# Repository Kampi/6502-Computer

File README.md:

# 6502 Computer

## Table of Contents

- [6502 Computer](#6502-computer)
  - [Table of Contents](#table-of-contents)
  - [About](#about)
  - [Examples](#examples)
  - [History](#history)
  - [Maintainer](#maintainer)

## About

A simple W65C02 based computer. This project should realize an old-style computer with peripheral interfaces like PS/2, LCD, VGA, etc.

Please check the [wiki](https://gitlab.com/Kampi/6502-computer/-/wikis/home) or write an e-mail to [DanielKampert@kampis-elektroecke.de](DanielKampert@kampis-elektroecke.de) if you have any questions.

> You can use [this](https://www.mouser.de/ProductDetail/Aries-Electronics/28-6554-11?qs=%2Fha2pyFaduhJzW47Xe0mc6AQy9aNg75kRj%2FLuQHFHUG0ReEYpRrMQA%3D%3D) ZIF socket for the EEPROM instead of the normal DIP socket for an easier mounting of the EEPROM.

## Tutorial

The `tutorial` folder of the repository contains the software examples from my [website](https://www.kampis-elektroecke.de/6502-computer/).

| **Tutorial** | **Description** |
|---|---|
| Lession 1 | Small program to check out how the compiler works and to test the communication between microprocessor, RAM and EEPROM. |
| Lession 2 | Simple program to learn the stack mechanics. |

## History

| **Version**  | **Description**                            	| **Date**   |
|:------------:|:----------------------------------------------:|:----------:|
| 0.1          | First hardware release.                     	| 18.10.2019 |
| 0.2          | Fix different hardware bugs, add new features. | 10.05.2021 |
| 0.3          |  |  |

## Maintainer

- [Daniel Kampert](mailto:DanielKampert@kampis-elektroecke.de)

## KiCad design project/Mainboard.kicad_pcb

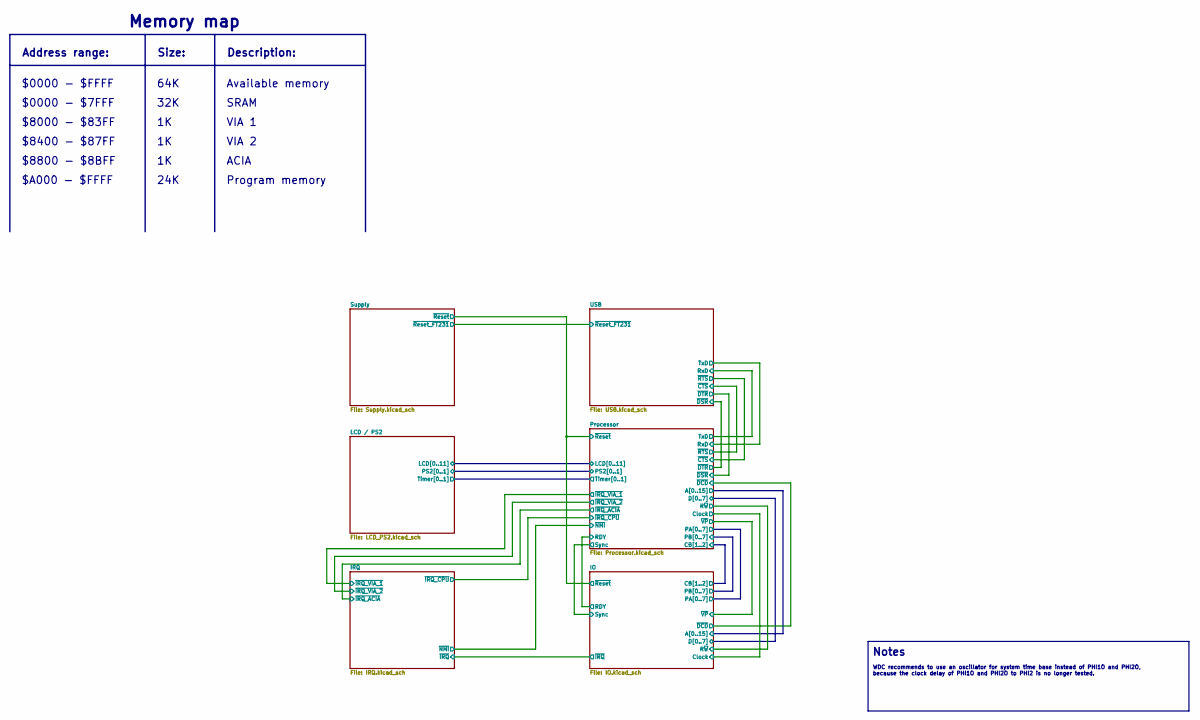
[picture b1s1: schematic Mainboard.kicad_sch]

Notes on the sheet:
$8000 - $83FF
Notes
$8400 - $87FF
64K
32K
ACIA
WDC recommends to use an oscillator for system time base instead of PHI1O and PHI2O, because the clock delay of PHI1O and PHI2O to PHI2 is no longer tested.
Size:
$8800 - $8BFF
Memory map
Program memory
Available memory
$0000 - $7FFF
SRAM
Address range:
24K
Description:
$0000 - $FFFF
$A000 - $FFFF
VIA 2
VIA 1

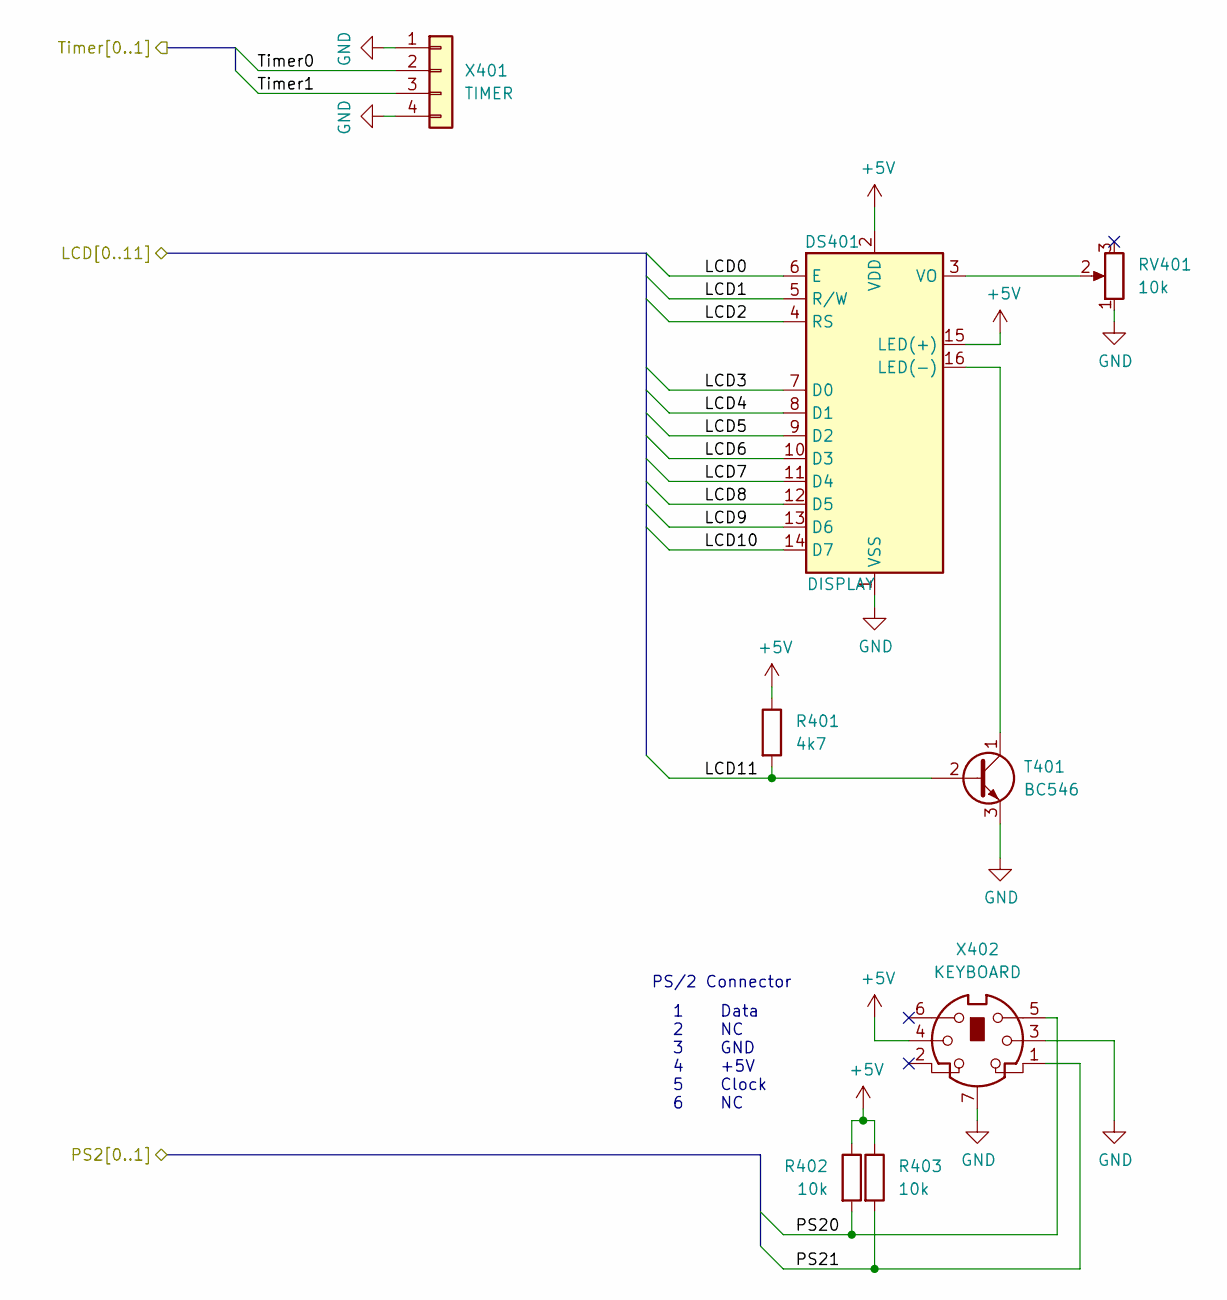
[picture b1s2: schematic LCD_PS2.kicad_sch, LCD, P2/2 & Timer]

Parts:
DS401: DISPLAY; WC1602A
R401: 4k7; R_Axial_DIN0207_L6.3mm_D2.5mm_P7.62mm_Horizontal
R402, R403: 10k; R_Axial_DIN0207_L6.3mm_D2.5mm_P7.62mm_Horizontal
RV401: 10k; Bourns_3386P_Vertical
T401: BC546; TO-92_Inline
X401: TIMER; PinHeader_1x04_P2.54mm_Vertical
X402: KEYBOARD; Mini-DIN_TE_Female_6Pin_2rows

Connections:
+5V: DS401.2 (VDD), DS401.15 (LED(+)), R401.1, R402.1, R403.1, X402.4; also elsewhere on the board
/LCD / PS2/LCD0: DS401.6 (E); also elsewhere on the board
/LCD / PS2/LCD1: DS401.5 (R/W); also elsewhere on the board
/LCD / PS2/LCD2: DS401.4 (RS); also elsewhere on the board
/LCD / PS2/LCD3: DS401.7 (D0); also elsewhere on the board
/LCD / PS2/LCD4: DS401.8 (D1); also elsewhere on the board
/LCD / PS2/LCD5: DS401.9 (D2); also elsewhere on the board
/LCD / PS2/LCD6: DS401.10 (D3); also elsewhere on the board
/LCD / PS2/LCD7: DS401.11 (D4); also elsewhere on the board
/LCD / PS2/LCD8: DS401.12 (D5); also elsewhere on the board
/LCD / PS2/LCD9: DS401.13 (D6); also elsewhere on the board
/LCD / PS2/LCD10: DS401.14 (D7); also elsewhere on the board
/LCD / PS2/LCD11: R401.2, T401.2 (B); also elsewhere on the board
/LCD / PS2/PS20: R402.2, X402.5; also elsewhere on the board
/LCD / PS2/PS21: R403.2, X402.1; also elsewhere on the board
/LCD / PS2/Timer0: X401.2; also elsewhere on the board
/LCD / PS2/Timer1: X401.3; also elsewhere on the board
GND: DS401.1 (VSS), RV401.1, T401.3 (E), X401.1, X401.4, X402.3, X402.7; also elsewhere on the board
unnamed: DS401.16 (LED(-)), T401.1 (C)
unnamed: DS401.3 (VO), RV401.2

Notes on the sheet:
PS/2 Connector
Data NC GND +5V Clock NC
1 2 3 4 5 6

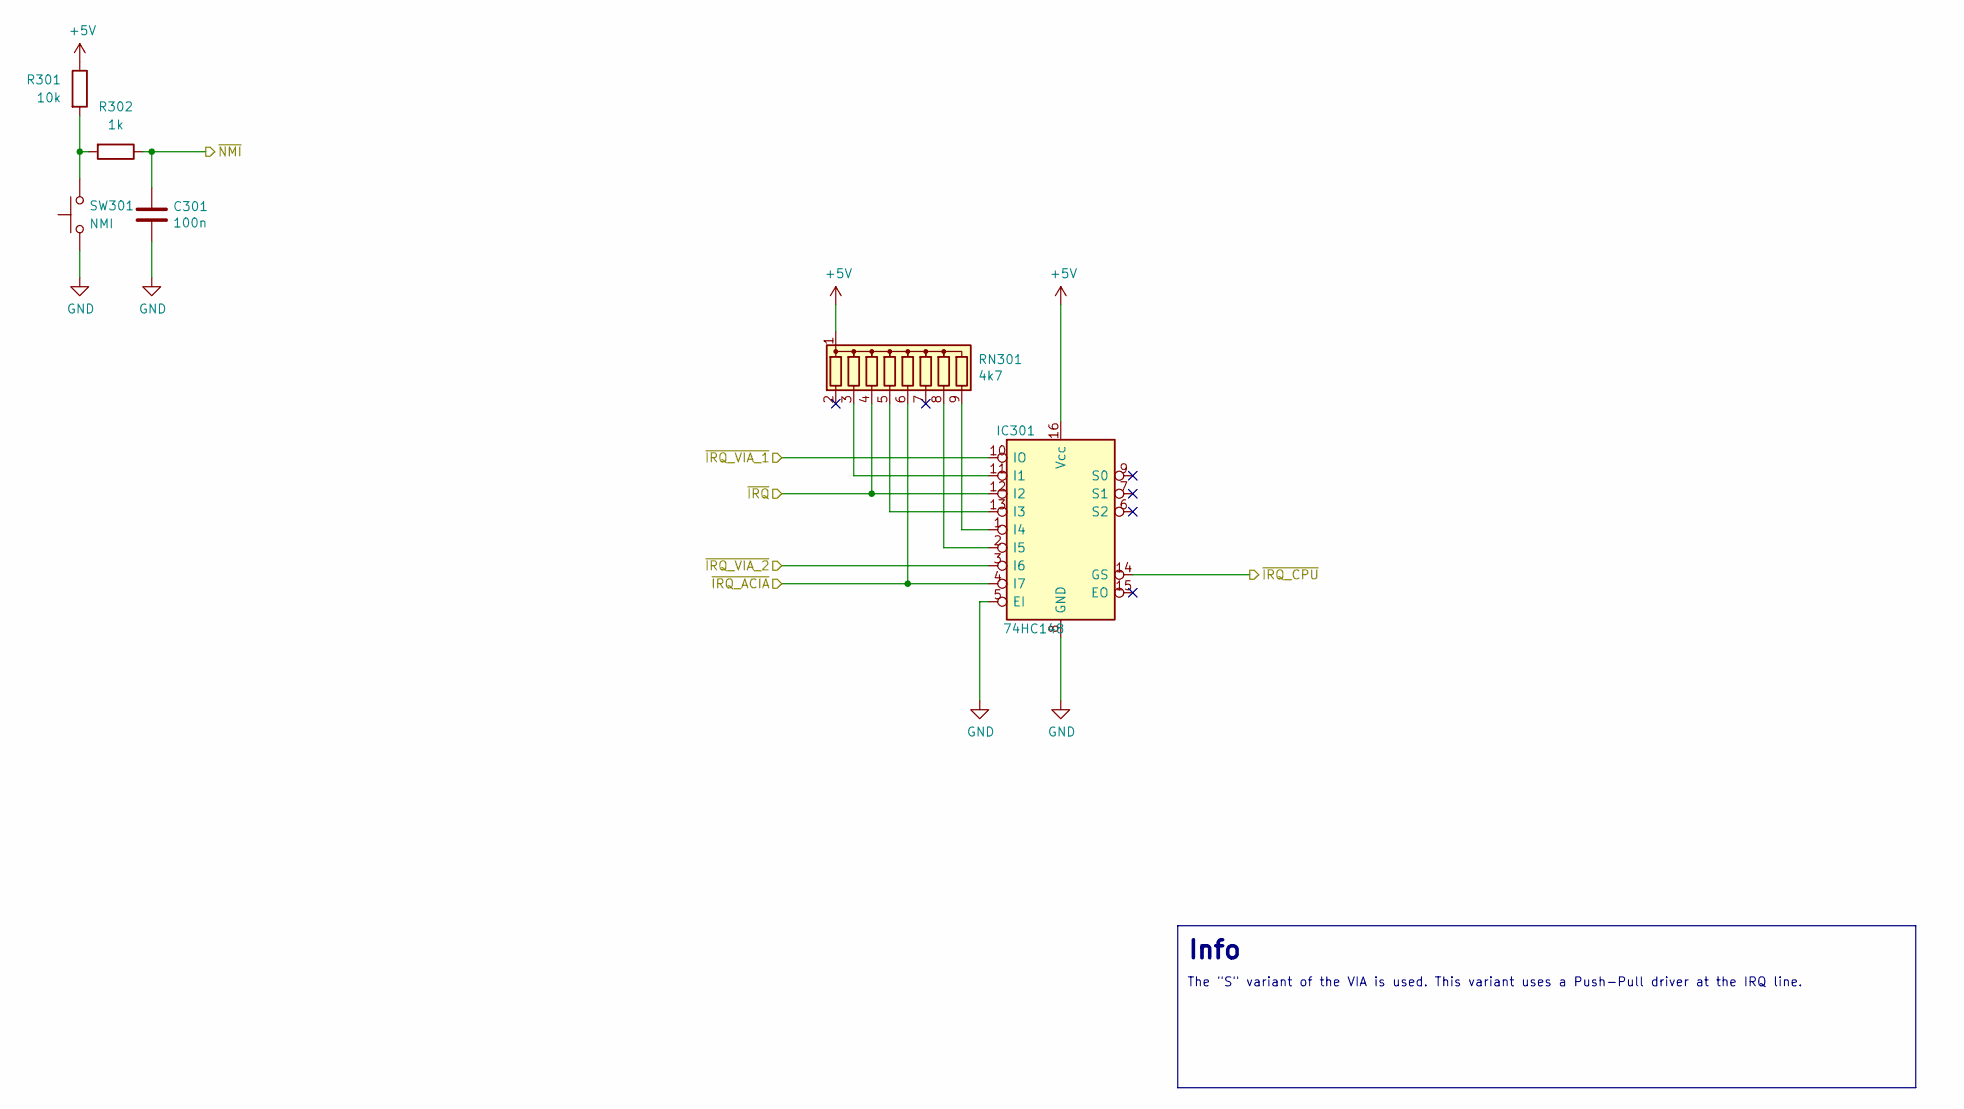
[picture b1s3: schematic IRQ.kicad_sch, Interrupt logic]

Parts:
C301: 100n; C_Rect_L4.0mm_W2.5mm_P2.50mm
IC301: 74HC148; DIP-16_W7.62mm_LongPads
R301: 10k; R_Axial_DIN0207_L6.3mm_D2.5mm_P7.62mm_Horizontal
R302: 1k; R_Axial_DIN0207_L6.3mm_D2.5mm_P7.62mm_Horizontal
RN301: 4k7; R_Array_SIP9
SW301: NMI; SW_PUSH_6mm_H4.3mm

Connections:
+5V: IC301.16 (Vcc), R301.1, RN301.1 (common); also elsewhere on the board
/IO/~IRQ: IC301.12 (I2), RN301.4 (R3); also elsewhere on the board
/IRQ/~IRQ_ACIA: IC301.4 (I7), RN301.6 (R5); also elsewhere on the board
/IRQ/~IRQ_CPU: IC301.14 (GS); also elsewhere on the board
/IRQ/~IRQ_VIA_1: IC301.10 (IO); also elsewhere on the board
/IRQ/~IRQ_VIA_2: IC301.3 (I6); also elsewhere on the board
/IRQ/~NMI: C301.1, R302.1; also elsewhere on the board
GND: C301.2, IC301.5 (EI), IC301.8 (GND), SW301.1; also elsewhere on the board
unnamed: IC301.11 (I1), RN301.3 (R2)
unnamed: IC301.13 (I3), RN301.5 (R4)
unnamed: IC301.1 (I4), RN301.9 (R8)
unnamed: IC301.2 (I5), RN301.8 (R7)
unnamed: R301.2, R302.2, SW301.2

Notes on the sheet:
Info
The "S" variant of the VIA is used. This variant uses a Push-Pull driver at the IRQ line.

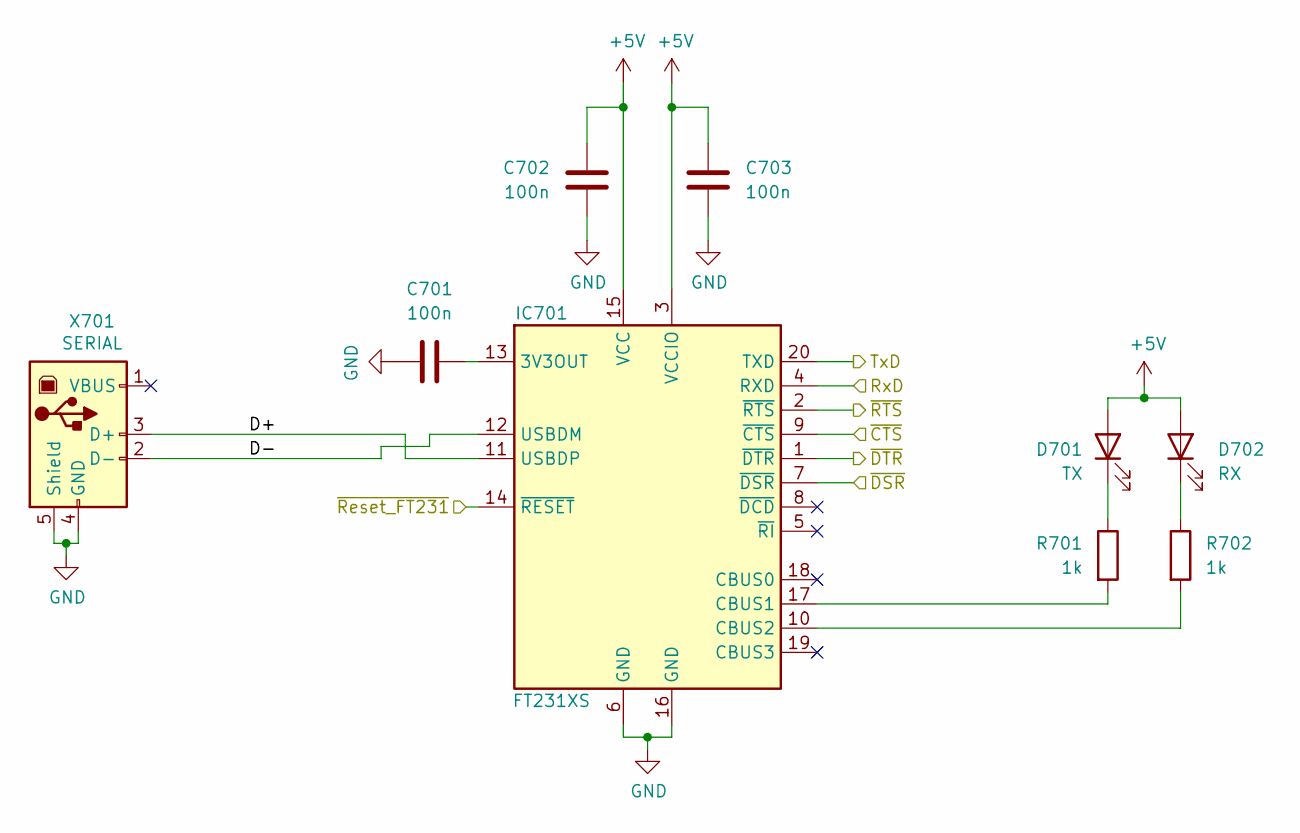
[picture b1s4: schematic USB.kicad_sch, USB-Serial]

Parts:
C701, C702, C703: 100n; C_0805_2012Metric
D701: TX; LED_0805_2012Metric
D702: RX; LED_0805_2012Metric
IC701: FT231XS; SSOP-20_3.9x8.7mm_P0.635mm
R701, R702: 1k; R_0805_2012Metric
X701: SERIAL; USB-B_TE_2923042_Horizontal

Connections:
+5V: C702.1, C703.1, D701.2 (A), D702.2 (A), IC701.3 (VCCIO), IC701.15 (VCC); also elsewhere on the board
/Processor/RxD: IC701.20 (TXD); also elsewhere on the board
/Processor/TxD: IC701.4 (RXD); also elsewhere on the board
/Processor/~CTS: IC701.2 (~RTS); also elsewhere on the board
/Processor/~DSR: IC701.1 (~DTR); also elsewhere on the board
/Processor/~DTR: IC701.7 (~DSR); also elsewhere on the board
/Processor/~RTS: IC701.9 (~CTS); also elsewhere on the board
/Supply/~Reset_FT231: IC701.14 (~RESET); also elsewhere on the board
/USB/D+: IC701.11 (USBDP), X701.3 (D+)
/USB/D-: IC701.12 (USBDM), X701.2 (D-)
GND: C701.1, C702.2, C703.2, IC701.6 (GND), IC701.16 (GND), X701.4 (GND), X701.5 (Shield); also elsewhere on the board
unnamed: D701.1 (K), R701.1
unnamed: D702.1 (K), R702.1
unnamed: C701.2, IC701.13 (3V3OUT)
unnamed: IC701.17 (CBUS1), R701.2
unnamed: IC701.10 (CBUS2), R702.2

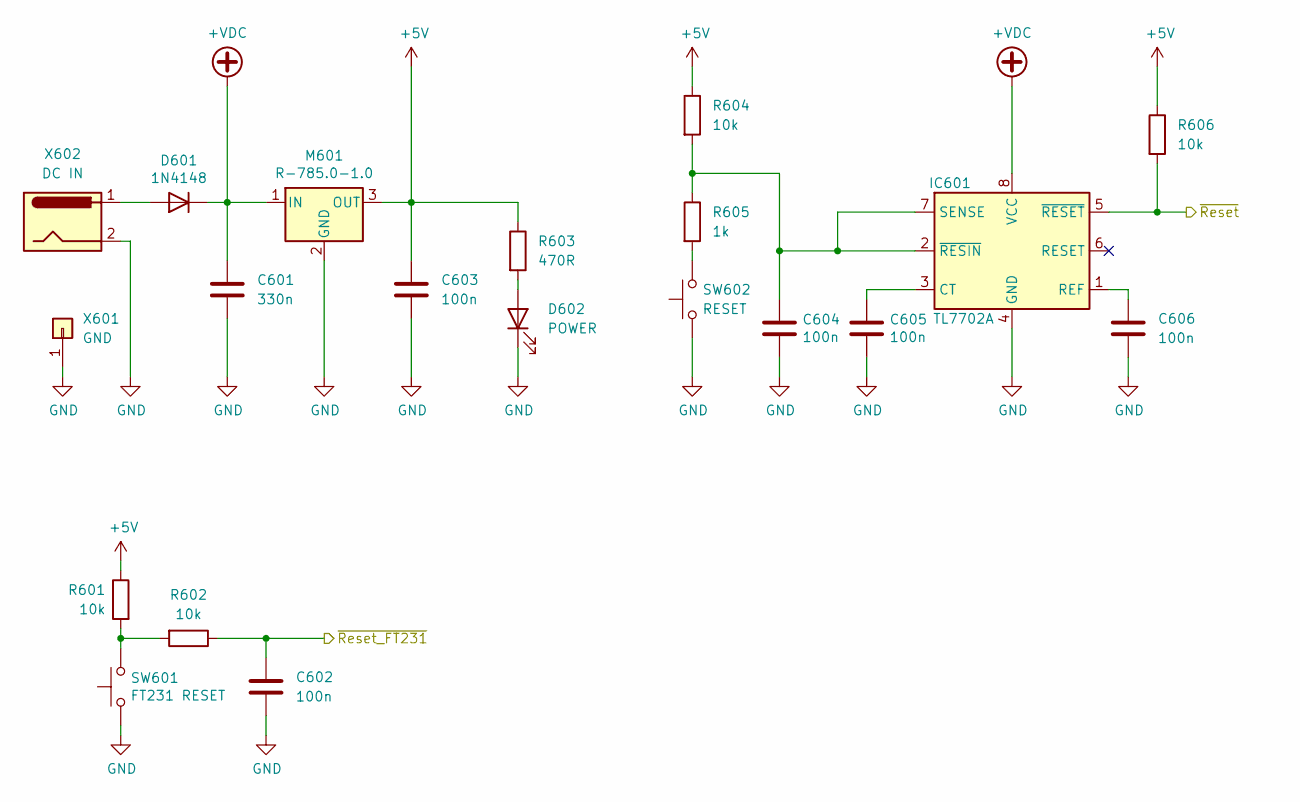
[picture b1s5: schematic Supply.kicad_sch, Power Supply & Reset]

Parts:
C601: 330n; C_Rect_L4.0mm_W2.5mm_P2.50mm
C602, C603, C604, C605, C606: 100n; C_Rect_L4.0mm_W2.5mm_P2.50mm
D601: 1N4148; D_SOD-123
D602: POWER; LED_D5.0mm
IC601: TL7702A; DIP-8_W7.62mm_LongPads
M601: R-785.0-1.0; Converter_DCDC_RECOM_R-78E-0.5_THT
R601, R602, R604, R606: 10k; R_Axial_DIN0207_L6.3mm_D2.5mm_P7.62mm_Horizontal
R603: 470R; R_Axial_DIN0207_L6.3mm_D2.5mm_P7.62mm_Horizontal
R605: 1k; R_Axial_DIN0207_L6.3mm_D2.5mm_P7.62mm_Horizontal
SW601: FT231 RESET; SW_PUSH_6mm_H4.3mm
SW602: RESET; SW_PUSH_6mm_H4.3mm
X601: GND; PinHeader_1x01_P2.54mm_Vertical
X602: DC IN; BarrelJack_Wuerth_6941xx301002

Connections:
+5V: C603.1, M601.3 (OUT), R601.1, R603.1, R604.1, R606.1; also elsewhere on the board
+VDC: C601.1, D601.1 (K), IC601.8 (VCC), M601.1 (IN)
/IO/~Reset: IC601.5 (~RESET), R606.2; also elsewhere on the board
/Supply/~Reset_FT231: C602.1, R602.1; also elsewhere on the board
GND: C601.2, C602.2, C603.2, C604.2, C605.2, C606.2, D602.1 (K), IC601.4 (GND), M601.2 (GND), SW601.1, SW602.1, X601.1, X602.2; also elsewhere on the board
unnamed: D601.2 (A), X602.1
unnamed: D602.2 (A), R603.2
unnamed: C605.1, IC601.3 (CT)
unnamed: C606.1, IC601.1 (REF)
unnamed: C604.1, IC601.2 (~RESIN), IC601.7 (SENSE), R604.2, R605.1
unnamed: R601.2, R602.2, SW601.2
unnamed: R605.2, SW602.2

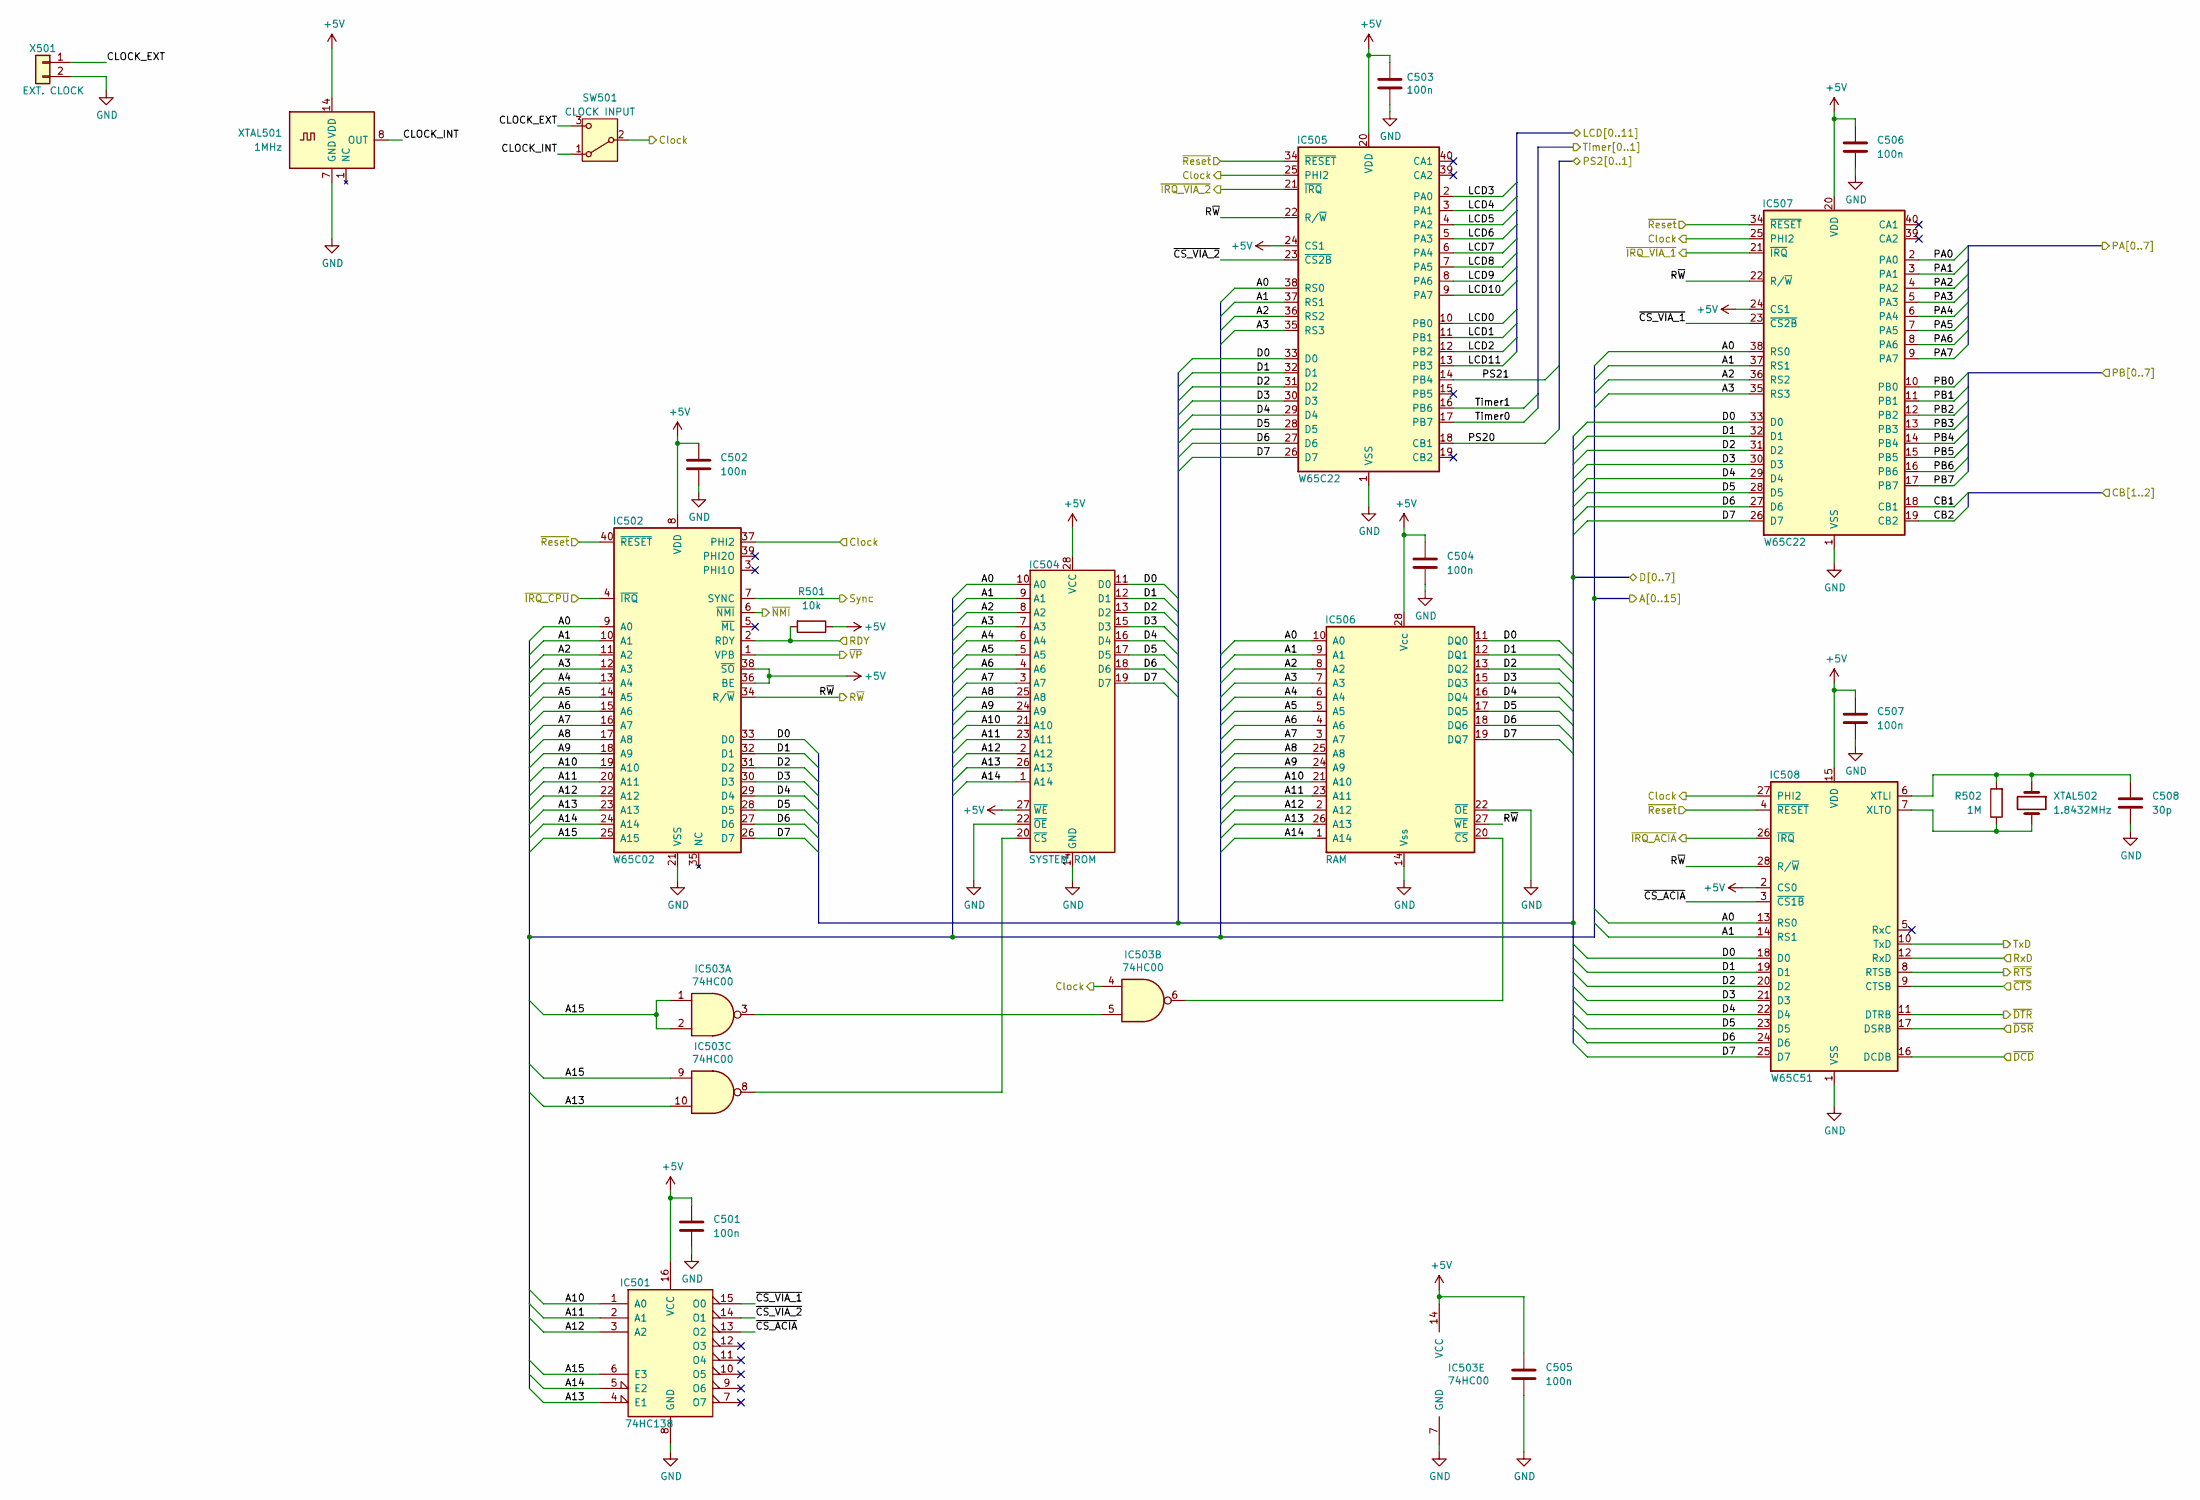
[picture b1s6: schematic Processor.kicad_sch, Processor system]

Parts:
C501, C502, C503, C504, C505, C506, C507: 100n; C_Rect_L4.0mm_W2.5mm_P2.50mm
C508: 30p; C_Rect_L4.0mm_W2.5mm_P2.50mm
IC501: 74HC138; DIP-16_W7.62mm_LongPads
IC502: W65C02; DIP-40_W15.24mm_LongPads
IC503: 74HC00; DIP-14_W7.62mm_LongPads
IC504: SYSTEM ROM; DIP-28_W15.24mm_LongPads
IC505, IC507: W65C22; DIP-40_W15.24mm_LongPads
IC506: RAM; DIP-28_W15.24mm_LongPads
IC508: W65C51; DIP-28_W15.24mm_LongPads
R501: 10k; R_Axial_DIN0207_L6.3mm_D2.5mm_P7.62mm_Horizontal
R502: 1M; R_Axial_DIN0207_L6.3mm_D2.5mm_P7.62mm_Horizontal
SW501: CLOCK INPUT; SW_E-Switch_EG1271_DPDT
X501: EXT. CLOCK; SMA_Amphenol_901-144_Vertical
XTAL501: 1MHz; Oscillator_DIP-14
XTAL502: 1.8432MHz; Crystal_HC49-U_Vertical

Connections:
+5V: C501.1, C502.1, C503.1, C504.1, C505.1, C506.1, C507.1, IC501.16 (VCC), IC502.8 (VDD), IC502.36 (BE), IC502.38 (~SO), IC503.14 (VCC), IC504.27 (~WE), IC504.28 (VCC), IC505.20 (VDD), IC505.24 (CS1), IC506.28 (Vcc), IC507.20 (VDD), IC507.24 (CS1), IC508.2 (CS0), IC508.15 (VDD), R501.1, XTAL501.14 (VDD); also elsewhere on the board
/IO/A0: IC502.9 (A0), IC504.10 (A0), IC505.38 (RS0), IC506.10 (A0), IC507.38 (RS0), IC508.13 (RS0); also elsewhere on the board
/IO/A1: IC502.10 (A1), IC504.9 (A1), IC505.37 (RS1), IC506.9 (A1), IC507.37 (RS1), IC508.14 (RS1); also elsewhere on the board
/IO/A2: IC502.11 (A2), IC504.8 (A2), IC505.36 (RS2), IC506.8 (A2), IC507.36 (RS2); also elsewhere on the board
/IO/A3: IC502.12 (A3), IC504.7 (A3), IC505.35 (RS3), IC506.7 (A3), IC507.35 (RS3); also elsewhere on the board
/IO/A4: IC502.13 (A4), IC504.6 (A4), IC506.6 (A4); also elsewhere on the board
/IO/A5: IC502.14 (A5), IC504.5 (A5), IC506.5 (A5); also elsewhere on the board
/IO/A6: IC502.15 (A6), IC504.4 (A6), IC506.4 (A6); also elsewhere on the board
/IO/A7: IC502.16 (A7), IC504.3 (A7), IC506.3 (A7); also elsewhere on the board
/IO/A8: IC502.17 (A8), IC504.25 (A8), IC506.25 (A8); also elsewhere on the board
/IO/A9: IC502.18 (A9), IC504.24 (A9), IC506.24 (A9); also elsewhere on the board
/IO/A10: IC501.1 (A0), IC502.19 (A10), IC504.21 (A10), IC506.21 (A10); also elsewhere on the board
/IO/A11: IC501.2 (A1), IC502.20 (A11), IC504.23 (A11), IC506.23 (A11); also elsewhere on the board
/IO/A12: IC501.3 (A2), IC502.22 (A12), IC504.2 (A12), IC506.2 (A12); also elsewhere on the board
/IO/A13: IC501.4 (E1), IC502.23 (A13), IC503.10, IC504.26 (A13), IC506.26 (A13); also elsewhere on the board
/IO/A14: IC501.5 (E2), IC502.24 (A14), IC504.1 (A14), IC506.1 (A14); also elsewhere on the board
/IO/A15: IC501.6 (E3), IC502.25 (A15), IC503.1, IC503.2, IC503.9; also elsewhere on the board
/IO/CB1: IC507.18 (CB1); also elsewhere on the board
/IO/CB2: IC507.19 (CB2); also elsewhere on the board
/IO/Clock: IC502.37 (PHI2), IC503.4, IC505.25 (PHI2), IC507.25 (PHI2), IC508.27 (PHI2), SW501.2 (B); also elsewhere on the board
/IO/D0: IC502.33 (D0), IC504.11 (D0), IC505.33 (D0), IC506.11 (DQ0), IC507.33 (D0), IC508.18 (D0); also elsewhere on the board
/IO/D1: IC502.32 (D1), IC504.12 (D1), IC505.32 (D1), IC506.12 (DQ1), IC507.32 (D1), IC508.19 (D1); also elsewhere on the board
/IO/D2: IC502.31 (D2), IC504.13 (D2), IC505.31 (D2), IC506.13 (DQ2), IC507.31 (D2), IC508.20 (D2); also elsewhere on the board
/IO/D3: IC502.30 (D3), IC504.15 (D3), IC505.30 (D3), IC506.15 (DQ3), IC507.30 (D3), IC508.21 (D3); also elsewhere on the board
/IO/D4: IC502.29 (D4), IC504.16 (D4), IC505.29 (D4), IC506.16 (DQ4), IC507.29 (D4), IC508.22 (D4); also elsewhere on the board
/IO/D5: IC502.28 (D5), IC504.17 (D5), IC505.28 (D5), IC506.17 (DQ5), IC507.28 (D5), IC508.23 (D5); also elsewhere on the board
/IO/D6: IC502.27 (D6), IC504.18 (D6), IC505.27 (D6), IC506.18 (DQ6), IC507.27 (D6), IC508.24 (D6); also elsewhere on the board
/IO/D7: IC502.26 (D7), IC504.19 (D7), IC505.26 (D7), IC506.19 (DQ7), IC507.26 (D7), IC508.25 (D7); also elsewhere on the board
/IO/PA0: IC507.2 (PA0); also elsewhere on the board
/IO/PA1: IC507.3 (PA1); also elsewhere on the board
/IO/PA2: IC507.4 (PA2); also elsewhere on the board
/IO/PA3: IC507.5 (PA3); also elsewhere on the board
/IO/PA4: IC507.6 (PA4); also elsewhere on the board
/IO/PA5: IC507.7 (PA5); also elsewhere on the board
/IO/PA6: IC507.8 (PA6); also elsewhere on the board
/IO/PA7: IC507.9 (PA7); also elsewhere on the board
/IO/PB0: IC507.10 (PB0); also elsewhere on the board
/IO/PB1: IC507.11 (PB1); also elsewhere on the board
/IO/PB2: IC507.12 (PB2); also elsewhere on the board
/IO/PB3: IC507.13 (PB3); also elsewhere on the board
/IO/PB4: IC507.14 (PB4); also elsewhere on the board
/IO/PB5: IC507.15 (PB5); also elsewhere on the board
/IO/PB6: IC507.16 (PB6); also elsewhere on the board
/IO/PB7: IC507.17 (PB7); also elsewhere on the board
/IO/RDY: IC502.2 (RDY), R501.2; also elsewhere on the board
/IO/Sync: IC502.7 (SYNC); also elsewhere on the board
/IO/~DCD: IC508.16 (DCDB); also elsewhere on the board
/IO/~Reset: IC502.40 (~RESET), IC505.34 (~RESET), IC507.34 (~RESET), IC508.4 (~RESET); also elsewhere on the board
/IO/~VP: IC502.1 (VPB); also elsewhere on the board
/IRQ/~IRQ_ACIA: IC508.26 (~IRQ); also elsewhere on the board
/IRQ/~IRQ_CPU: IC502.4 (~IRQ); also elsewhere on the board
/IRQ/~IRQ_VIA_1: IC507.21 (~IRQ); also elsewhere on the board
/IRQ/~IRQ_VIA_2: IC505.21 (~IRQ); also elsewhere on the board
/IRQ/~NMI: IC502.6 (~NMI); also elsewhere on the board
/LCD / PS2/LCD0: IC505.10 (PB0); also elsewhere on the board
/LCD / PS2/LCD1: IC505.11 (PB1); also elsewhere on the board
/LCD / PS2/LCD2: IC505.12 (PB2); also elsewhere on the board
/LCD / PS2/LCD3: IC505.2 (PA0); also elsewhere on the board
/LCD / PS2/LCD4: IC505.3 (PA1); also elsewhere on the board
/LCD / PS2/LCD5: IC505.4 (PA2); also elsewhere on the board
/LCD / PS2/LCD6: IC505.5 (PA3); also elsewhere on the board
/LCD / PS2/LCD7: IC505.6 (PA4); also elsewhere on the board
/LCD / PS2/LCD8: IC505.7 (PA5); also elsewhere on the board
/LCD / PS2/LCD9: IC505.8 (PA6); also elsewhere on the board
/LCD / PS2/LCD10: IC505.9 (PA7); also elsewhere on the board
/LCD / PS2/LCD11: IC505.13 (PB3); also elsewhere on the board
/LCD / PS2/PS20: IC505.18 (CB1); also elsewhere on the board
/LCD / PS2/PS21: IC505.14 (PB4); also elsewhere on the board
/LCD / PS2/Timer0: IC505.17 (PB7); also elsewhere on the board
/LCD / PS2/Timer1: IC505.16 (PB6); also elsewhere on the board
/Processor/CLOCK_EXT: SW501.3 (C), X501.1
/Processor/CLOCK_INT: SW501.1 (A), XTAL501.8 (OUT)
/Processor/RxD: IC508.12 (RxD); also elsewhere on the board
/Processor/R~W: IC502.34 (R/~W), IC505.22 (R/~W), IC506.27 (~WE), IC507.22 (R/~W), IC508.28 (R/~W); also elsewhere on the board
/Processor/TxD: IC508.10 (TxD); also elsewhere on the board
/Processor/~CS_ACIA: IC501.13 (O2), IC508.3 (~CS1B)
/Processor/~CS_VIA_1: IC501.15 (O0), IC507.23 (~CS2B)
/Processor/~CS_VIA_2: IC501.14 (O1), IC505.23 (~CS2B)
/Processor/~CTS: IC508.9 (CTSB); also elsewhere on the board
/Processor/~DSR: IC508.17 (DSRB); also elsewhere on the board
/Processor/~DTR: IC508.11 (DTRB); also elsewhere on the board
/Processor/~RTS: IC508.8 (RTSB); also elsewhere on the board
GND: C501.2, C502.2, C503.2, C504.2, C505.2, C506.2, C507.2, C508.2, IC501.8 (GND), IC502.21 (VSS), IC503.7 (GND), IC504.14 (GND), IC504.22 (~OE), IC505.1 (VSS), IC506.14 (Vss), IC506.22 (~OE), IC507.1 (VSS), IC508.1 (VSS), X501.2, XTAL501.7 (GND); also elsewhere on the board
unnamed: IC503.3, IC503.5
unnamed: IC503.8, IC504.20 (~CS)
unnamed: IC503.6, IC506.20 (~CS)
unnamed: IC508.7 (XLTO), R502.1, XTAL502.2
unnamed: C508.1, IC508.6 (XTLI), R502.2, XTAL502.1

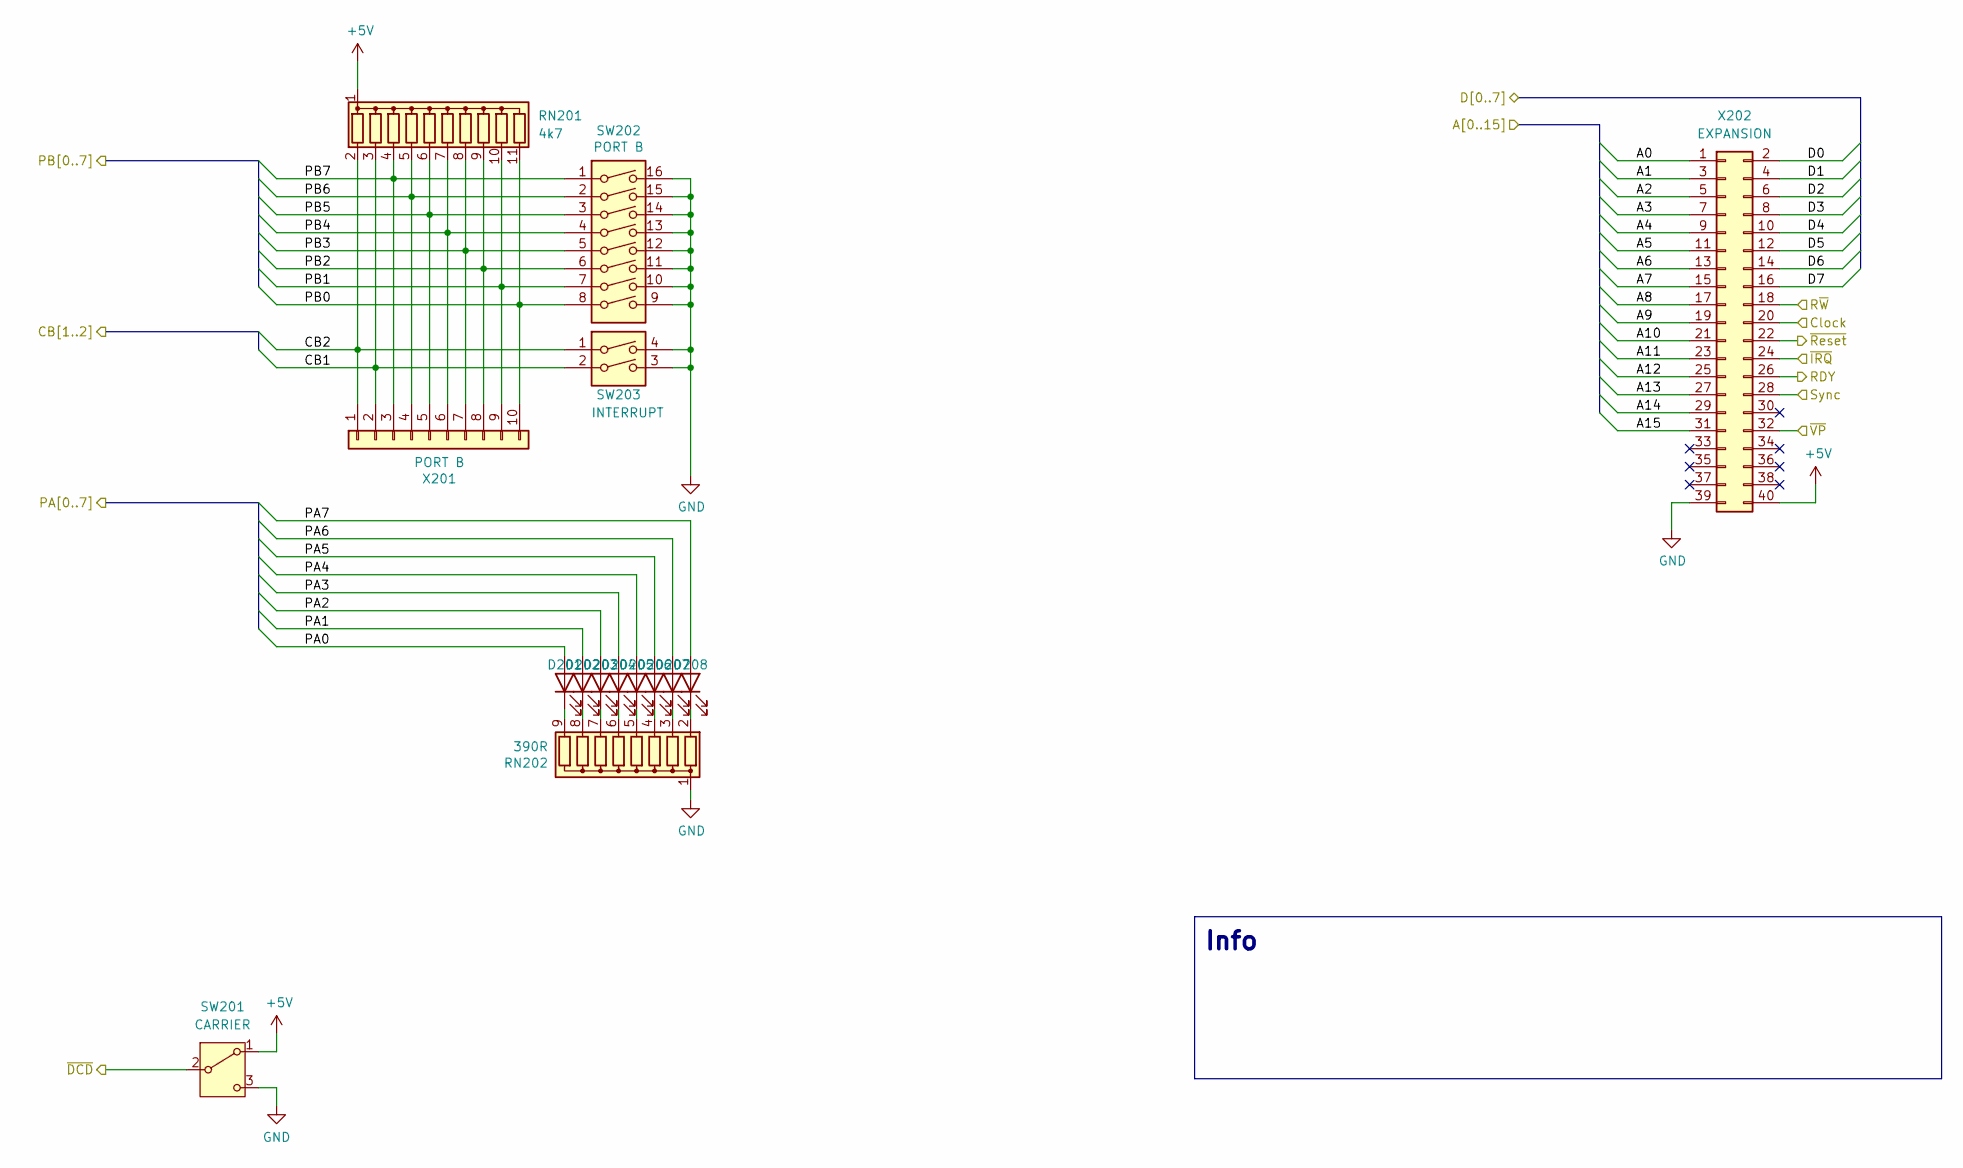
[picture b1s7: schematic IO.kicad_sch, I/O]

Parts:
D201: LED0; LED_D5.0mm
D202: LED1; LED_D5.0mm
D203: LED2; LED_D5.0mm
D204: LED3; LED_D5.0mm
D205: LED4; LED_D5.0mm
D206: LED5; LED_D5.0mm
D207: LED6; LED_D5.0mm
D208: LED7; LED_D5.0mm
RN201: 4k7; R_Array_SIP11
RN202: 390R; R_Array_SIP9
SW201: CARRIER; SW_E-Switch_EG1224_SPDT_Angled
SW202: PORT B; SW_DIP_SPSTx08_Slide_9.78x22.5mm_W7.62mm_P2.54mm
SW203: INTERRUPT; SW_DIP_SPSTx02_Slide_9.78x7.26mm_W7.62mm_P2.54mm
X201: PORT B; PinHeader_1x10_P2.54mm_Vertical
X202: EXPANSION; PinHeader_2x20_P2.54mm_Horizontal

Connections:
+5V: RN201.1 (common), SW201.1 (A), X202.40; also elsewhere on the board
/IO/A0: X202.1; also elsewhere on the board
/IO/A1: X202.3; also elsewhere on the board
/IO/A2: X202.5; also elsewhere on the board
/IO/A3: X202.7; also elsewhere on the board
/IO/A4: X202.9; also elsewhere on the board
/IO/A5: X202.11; also elsewhere on the board
/IO/A6: X202.13; also elsewhere on the board
/IO/A7: X202.15; also elsewhere on the board
/IO/A8: X202.17; also elsewhere on the board
/IO/A9: X202.19; also elsewhere on the board
/IO/A10: X202.21; also elsewhere on the board
/IO/A11: X202.23; also elsewhere on the board
/IO/A12: X202.25; also elsewhere on the board
/IO/A13: X202.27; also elsewhere on the board
/IO/A14: X202.29; also elsewhere on the board
/IO/A15: X202.31; also elsewhere on the board
/IO/CB1: RN201.3 (R2), SW203.2, X201.2; also elsewhere on the board
/IO/CB2: RN201.2 (R1), SW203.1, X201.1; also elsewhere on the board
/IO/Clock: X202.20; also elsewhere on the board
/IO/D0: X202.2; also elsewhere on the board
/IO/D1: X202.4; also elsewhere on the board
/IO/D2: X202.6; also elsewhere on the board
/IO/D3: X202.8; also elsewhere on the board
/IO/D4: X202.10; also elsewhere on the board
/IO/D5: X202.12; also elsewhere on the board
/IO/D6: X202.14; also elsewhere on the board
/IO/D7: X202.16; also elsewhere on the board
/IO/PA0: D201.2 (A); also elsewhere on the board
/IO/PA1: D202.2 (A); also elsewhere on the board
/IO/PA2: D203.2 (A); also elsewhere on the board
/IO/PA3: D204.2 (A); also elsewhere on the board
/IO/PA4: D205.2 (A); also elsewhere on the board
/IO/PA5: D206.2 (A); also elsewhere on the board
/IO/PA6: D207.2 (A); also elsewhere on the board
/IO/PA7: D208.2 (A); also elsewhere on the board
/IO/PB0: RN201.11 (R10), SW202.8, X201.10; also elsewhere on the board
/IO/PB1: RN201.10 (R9), SW202.7, X201.9; also elsewhere on the board
/IO/PB2: RN201.9 (R8), SW202.6, X201.8; also elsewhere on the board
/IO/PB3: RN201.8 (R7), SW202.5, X201.7; also elsewhere on the board
/IO/PB4: RN201.7 (R6), SW202.4, X201.6; also elsewhere on the board
/IO/PB5: RN201.6 (R5), SW202.3, X201.5; also elsewhere on the board
/IO/PB6: RN201.5 (R4), SW202.2, X201.4; also elsewhere on the board
/IO/PB7: RN201.4 (R3), SW202.1, X201.3; also elsewhere on the board
/IO/RDY: X202.26; also elsewhere on the board
/IO/Sync: X202.28; also elsewhere on the board
/IO/~DCD: SW201.2 (B); also elsewhere on the board
/IO/~IRQ: X202.24; also elsewhere on the board
/IO/~Reset: X202.22; also elsewhere on the board
/IO/~VP: X202.32; also elsewhere on the board
/Processor/R~W: X202.18; also elsewhere on the board
GND: RN202.1 (common), SW201.3 (C), SW202.9, SW202.10, SW202.11, SW202.12, SW202.13, SW202.14, SW202.15, SW202.16, SW203.3, SW203.4, X202.39; also elsewhere on the board
unnamed: D201.1 (K), RN202.9 (R8)
unnamed: D202.1 (K), RN202.8 (R7)
unnamed: D203.1 (K), RN202.7 (R6)
unnamed: D204.1 (K), RN202.6 (R5)
unnamed: D205.1 (K), RN202.5 (R4)
unnamed: D206.1 (K), RN202.4 (R3)
unnamed: D207.1 (K), RN202.3 (R2)
unnamed: D208.1 (K), RN202.2 (R1)

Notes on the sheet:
Info
